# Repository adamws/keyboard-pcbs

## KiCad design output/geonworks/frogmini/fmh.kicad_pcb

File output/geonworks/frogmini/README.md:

## geonworks/frogmini/fmh

[layout](fmh-kle.json) - [PCB](fmh.kicad_pcb)

{:loading="lazy"}

[Open in keyboard-layout-editor](http://www.keyboard-layout-editor.com/##@@_x:2.5&y:1.25&c=#777777;&=0,0&_c=#cccccc;&=0,1&=0,2&=0,3&=0,4&=0,5&=0,6&=0,7&=0,8&=0,9&=0,10&=0,11&=0,12&_c=#aaaaaa&w:2;&=0,13%0A%0A%0A0,0;&@_x:2.5&w:1.5;&=1,0&_c=#cccccc;&=1,1&=1,2&=1,3&=1,4&=1,5&=1,6&=1,7&=1,8&=1,9&=1,10&=1,11&=1,12&_w:1.5;&=1,13;&@_x:2.5&c=#aaaaaa&w:1.75;&=2,0&_c=#cccccc;&=2,1&=2,2&=2,3&=2,4&=2,5&=2,6&=2,7&=2,8&=2,9&=2,10&=2,11&_c=#777777&w:2.25;&=2,13;&@_x:2.5&c=#aaaaaa&w:2.25;&=3,0&_c=#cccccc;&=3,2&=3,3&=3,4&=3,5&=3,6&=3,7&=3,8&=3,9&=3,10&=3,11&_c=#aaaaaa&w:2.75;&=3,12%0A%0A%0A1,0;&@_x:2.5&w:1.5;&=4,0%0A%0A%0A2,0&=4,1%0A%0A%0A2,0&_w:1.5;&=4,2%0A%0A%0A2,0&_c=#cccccc&w:7;&=5,6%0A%0A%0A2,0&_c=#aaaaaa&w:1.5;&=5,10%0A%0A%0A2,0&=5,11%0A%0A%0A2,0&_w:1.5;&=5,12%0A%0A%0A2,0;&@_x:15.5&y:-6.25&c=#cccccc;&=0,13%0A%0A%0A0,1&=5,13%0A%0A%0A0,1;&@_x:17.75&y:3.25&c=#aaaaaa&w:1.75;&=3,12%0A%0A%0A1,1&_c=#cccccc;&=3,13%0A%0A%0A1,1;&@_x:2.5&y:1.25&c=#aaaaaa&w:1.5&d:true;&=4,0%0A%0A%0A2,1&=4,1%0A%0A%0A2,1&_w:1.5;&=4,2%0A%0A%0A2,1&_c=#cccccc&w:7;&=5,6%0A%0A%0A2,1&_c=#aaaaaa&w:1.5;&=5,10%0A%0A%0A2,1&=5,11%0A%0A%0A2,1&_w:1.5&d:true;&=5,12%0A%0A%0A2,1;&@_x:2.5&y:0.25&w:1.5;&=4,0%0A%0A%0A2,2&_x:1.0&w:1.5;&=4,2%0A%0A%0A2,2&_c=#cccccc&w:7;&=5,6%0A%0A%0A2,2&_c=#aaaaaa&w:1.5;&=5,10%0A%0A%0A2,2&_x:1.0&w:1.5;&=5,12%0A%0A%0A2,2)

{:loading="lazy"}

## geonworks/frogmini/fms

[layout](fms-kle.json) - [PCB](fms.kicad_pcb)

{:loading="lazy"}

[Open in keyboard-layout-editor](http://www.keyboard-layout-editor.com/##@@_x:2.5&y:1.25&c=#777777;&=0,0&_c=#cccccc;&=0,1&=0,2&=0,3&=0,4&=0,5&=0,6&=0,7&=0,8&=0,9&=0,10&=0,11&=0,12&_c=#aaaaaa&w:2;&=0,13%0A%0A%0A0,0;&@_x:2.5&w:1.5;&=1,0&_c=#cccccc;&=1,1&=1,2&=1,3&=1,4&=1,5&=1,6&=1,7&=1,8&=1,9&=1,10&=1,11&=1,12&_w:1.5;&=1,13%0A%0A%0A1,0;&@_x:2.5&c=#aaaaaa&w:1.75;&=2,0&_c=#cccccc;&=2,1&=2,2&=2,3&=2,4&=2,5&=2,6&=2,7&=2,8&=2,9&=2,10&=2,11&_c=#777777&w:2.25;&=2,13%0A%0A%0A1,0;&@_x:2.5&c=#aaaaaa&w:2.25;&=3,0%0A%0A%0A2,0&_c=#cccccc;&=3,2&=3,3&=3,4&=3,5&=3,6&=3,7&=3,8&=3,9&=3,10&=3,11&_c=#aaaaaa&w:2.75;&=3,12%0A%0A%0A3,0;&@_x:2.5&w:1.25;&=4,0%0A%0A%0A4,0&_w:1.25;&=4,1%0A%0A%0A4,0&_w:1.25;&=4,2%0A%0A%0A4,0&_c=#cccccc&w:6.25;&=5,6%0A%0A%0A4,0&_c=#aaaaaa&w:1.25;&=5,9%0A%0A%0A4,0&_w:1.25;&=5,10%0A%0A%0A4,0&_w:1.25;&=5,11%0A%0A%0A4,0&_w:1.25;&=5,12%0A%0A%0A4,0;&@_x:15.5&y:-6.25&c=#cccccc;&=0,13%0A%0A%0A0,1&=5,13%0A%0A%0A0,1;&@_x:19.25&y:1.25&c=#777777&w:1.25&h:2&w2:1.5&h2:1&x2:-0.25;&=2,13%0A%0A%0A1,1;&@_x:18.25&c=#cccccc;&=2,12%0A%0A%0A1,1;&@_w:1.25;&=3,0%0A%0A%0A2,1&=3,1%0A%0A%0A2,1&_x:15.5&c=#aaaaaa&w:1.75;&=3,12%0A%0A%0A3,1&_c=#cccccc;&=3,13%0A%0A%0A3,1;&@_x:2.5&y:1.25&c=#aaaaaa&w:1.5;&=4,0%0A%0A%0A4,1&=4,1%0A%0A%0A4,1&_w:1.5;&=4,2%0A%0A%0A4,1&_c=#cccccc&w:7;&=5,6%0A%0A%0A4,1&_c=#aaaaaa&w:1.5;&=5,10%0A%0A%0A4,1&=5,11%0A%0A%0A4,1&_w:1.5;&=5,12%0A%0A%0A4,1;&@_x:2.5&y:0.25&w:1.5&d:true;&=4,0%0A%0A%0A4,2&=4,1%0A%0A%0A4,2&_w:1.5;&=4,2%0A%0A%0A4,2&_c=#cccccc&w:7;&=5,6%0A%0A%0A4,2&_c=#aaaaaa&w:1.5;&=5,10%0A%0A%0A4,2&=5,11%0A%0A%0A4,2&_w:1.5&d:true;&=5,12%0A%0A%0A4,2;&@_x:2.5&y:0.25&w:1.5;&=4,0%0A%0A%0A4,3&_d:true;&=4,1%0A%0A%0A4,3&_w:1.5;&=4,2%0A%0A%0A4,3&_c=#cccccc&w:7;&=5,6%0A%0A%0A4,3&_c=#aaaaaa&w:1.5;&=5,10%0A%0A%0A4,3&_d:true;&=5,11%0A%0A%0A4,3&_w:1.5;&=5,12%0A%0A%0A4,3;&@_x:2.5&y:0.25&w:1.5;&=4,0%0A%0A%0A4,4&=4,1%0A%0A%0A4,4&_c=#cccccc&w:10;&=5,6%0A%0A%0A4,4&_c=#aaaaaa;&=5,11%0A%0A%0A4,4&_w:1.5;&=5,12%0A%0A%0A4,4;&@_x:2.5&y:0.25&w:1.5&d:true;&=4,0%0A%0A%0A4,5&=4,1%0A%0A%0A4,5&_c=#cccccc&w:10;&=5,6%0A%0A%0A4,5&_c=#aaaaaa;&=5,11%0A%0A%0A4,5&_w:1.5&d:true;&=5,12%0A%0A%0A4,5;&@_x:2.5&y:0.25&w:1.5;&=4,0%0A%0A%0A4,6&_d:true;&=4,1%0A%0A%0A4,6&_c=#cccccc&w:10;&=5,6%0A%0A%0A4,6&_c=#aaaaaa&d:true;&=5,11%0A%0A%0A4,6&_w:1.5;&=5,12%0A%0A%0A4,6)

{:loading="lazy"}

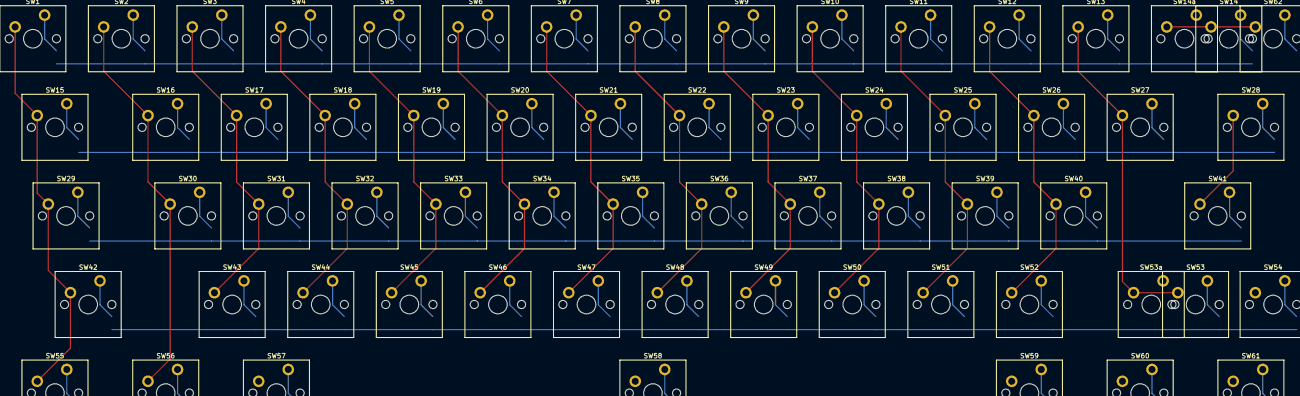
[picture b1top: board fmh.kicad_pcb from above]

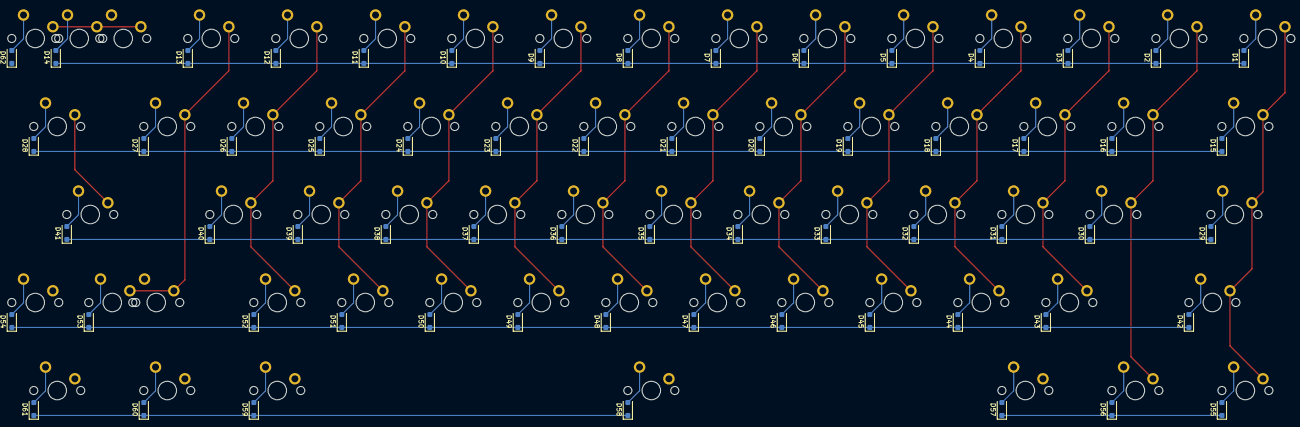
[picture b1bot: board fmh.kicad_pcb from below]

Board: 2 copper layers, 126 parts (62 on the bottom side), 82 nets.

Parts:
D1, D2, D3, D4, D5, D6, D7, D8, D9, D10, D11, D12, D13, D14, D15, D16, D17, D18, D19, D20, D21, D22, D23, D24, D25, D26, D27, D28, D29, D30, D31, D32, D33, D34, D35, D36, D37, D38, D39, D40, D41, D42, D43, D44, D45, D46, D47, D48, D49, D50, D51, D52, D53, D54, D55, D56, D57, D58, D59, D60, D61, D62: D_SOD-123F
SW1, SW2, SW3, SW4, SW5, SW6, SW7, SW8, SW9, SW10, SW11, SW12, SW13, SW14, SW14a, SW15, SW16, SW17, SW18, SW19, SW20, SW21, SW22, SW23, SW24, SW25, SW26, SW27, SW28, SW29, SW30, SW31, SW32, SW33, SW34, SW35, SW36, SW37, SW38, SW39, SW40, SW41, SW42, SW43, SW44, SW45, SW46, SW47, SW48, SW49, SW50, SW51, SW52, SW53, SW53a, SW54, SW55, SW56, SW57, SW58, SW59, SW60, SW61, SW62: SW_Cherry_MX_PCB_1.00u

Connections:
COL0: SW1.1, SW15.1, SW29.1, SW42.1, SW55.1
COL1: SW2.1, SW16.1, SW30.1, SW56.1
COL2: SW3.1, SW17.1, SW31.1, SW43.1, SW57.1
COL3: SW4.1, SW18.1, SW32.1, SW44.1
COL4: SW5.1, SW19.1, SW33.1, SW45.1
COL5: SW6.1, SW20.1, SW34.1, SW46.1
COL6: SW7.1, SW21.1, SW35.1, SW47.1, SW58.1
COL7: SW8.1, SW22.1, SW36.1, SW48.1
COL8: SW9.1, SW23.1, SW37.1, SW49.1
COL9: SW10.1, SW24.1, SW38.1, SW50.1
COL10: SW11.1, SW25.1, SW39.1, SW51.1, SW59.1
COL11: SW12.1, SW26.1, SW40.1, SW52.1, SW60.1
COL12: SW13.1, SW27.1, SW53.1, SW53a.1, SW61.1
COL13: SW14.1, SW14a.1, SW28.1, SW41.1, SW54.1, SW62.1
unnamed: D1.2, SW1.2
unnamed: D2.2, SW2.2
unnamed: D3.2, SW3.2
unnamed: D4.2, SW4.2
unnamed: D5.2, SW5.2
unnamed: D6.2, SW6.2
unnamed: D7.2, SW7.2
unnamed: D8.2, SW8.2
unnamed: D9.2, SW9.2
unnamed: D10.2, SW10.2
unnamed: D11.2, SW11.2
unnamed: D12.2, SW12.2
unnamed: D13.2, SW13.2
unnamed: D14.2, SW14.2, SW14a.2
unnamed: D15.2, SW15.2
unnamed: D16.2, SW16.2
unnamed: D17.2, SW17.2
unnamed: D18.2, SW18.2
unnamed: D19.2, SW19.2
unnamed: D20.2, SW20.2
unnamed: D21.2, SW21.2
unnamed: D22.2, SW22.2
unnamed: D23.2, SW23.2
unnamed: D24.2, SW24.2
unnamed: D25.2, SW25.2
unnamed: D26.2, SW26.2
unnamed: D27.2, SW27.2
unnamed: D28.2, SW28.2
unnamed: D29.2, SW29.2
unnamed: D30.2, SW30.2
unnamed: D31.2, SW31.2
unnamed: D32.2, SW32.2
unnamed: D33.2, SW33.2
unnamed: D34.2, SW34.2
unnamed: D35.2, SW35.2
unnamed: D36.2, SW36.2
unnamed: D37.2, SW37.2
unnamed: D38.2, SW38.2
unnamed: D39.2, SW39.2
unnamed: D40.2, SW40.2
unnamed: D41.2, SW41.2
unnamed: D42.2, SW42.2
unnamed: D43.2, SW43.2
unnamed: D44.2, SW44.2
unnamed: D45.2, SW45.2
unnamed: D46.2, SW46.2
unnamed: D47.2, SW47.2
unnamed: D48.2, SW48.2
unnamed: D49.2, SW49.2
unnamed: D50.2, SW50.2
unnamed: D51.2, SW51.2
unnamed: D52.2, SW52.2
unnamed: D53.2, SW53.2, SW53a.2
unnamed: D54.2, SW54.2
unnamed: D55.2, SW55.2
unnamed: D56.2, SW56.2
unnamed: D57.2, SW57.2
unnamed: D58.2, SW58.2
unnamed: D59.2, SW59.2
unnamed: D60.2, SW60.2
unnamed: D61.2, SW61.2
unnamed: D62.2, SW62.2
ROW0: D1.1, D2.1, D3.1, D4.1, D5.1, D6.1, D7.1, D8.1, D9.1, D10.1, D11.1, D12.1, D13.1, D14.1
ROW1: D15.1, D16.1, D17.1, D18.1, D19.1, D20.1, D21.1, D22.1, D23.1, D24.1, D25.1, D26.1, D27.1, D28.1
ROW2: D29.1, D30.1, D31.1, D32.1, D33.1, D34.1, D35.1, D36.1, D37.1, D38.1, D39.1, D40.1, D41.1
ROW3: D42.1, D43.1, D44.1, D45.1, D46.1, D47.1, D48.1, D49.1, D50.1, D51.1, D52.1, D53.1, D54.1
ROW4: D55.1, D56.1, D57.1
ROW5: D58.1, D59.1, D60.1, D61.1, D62.1
